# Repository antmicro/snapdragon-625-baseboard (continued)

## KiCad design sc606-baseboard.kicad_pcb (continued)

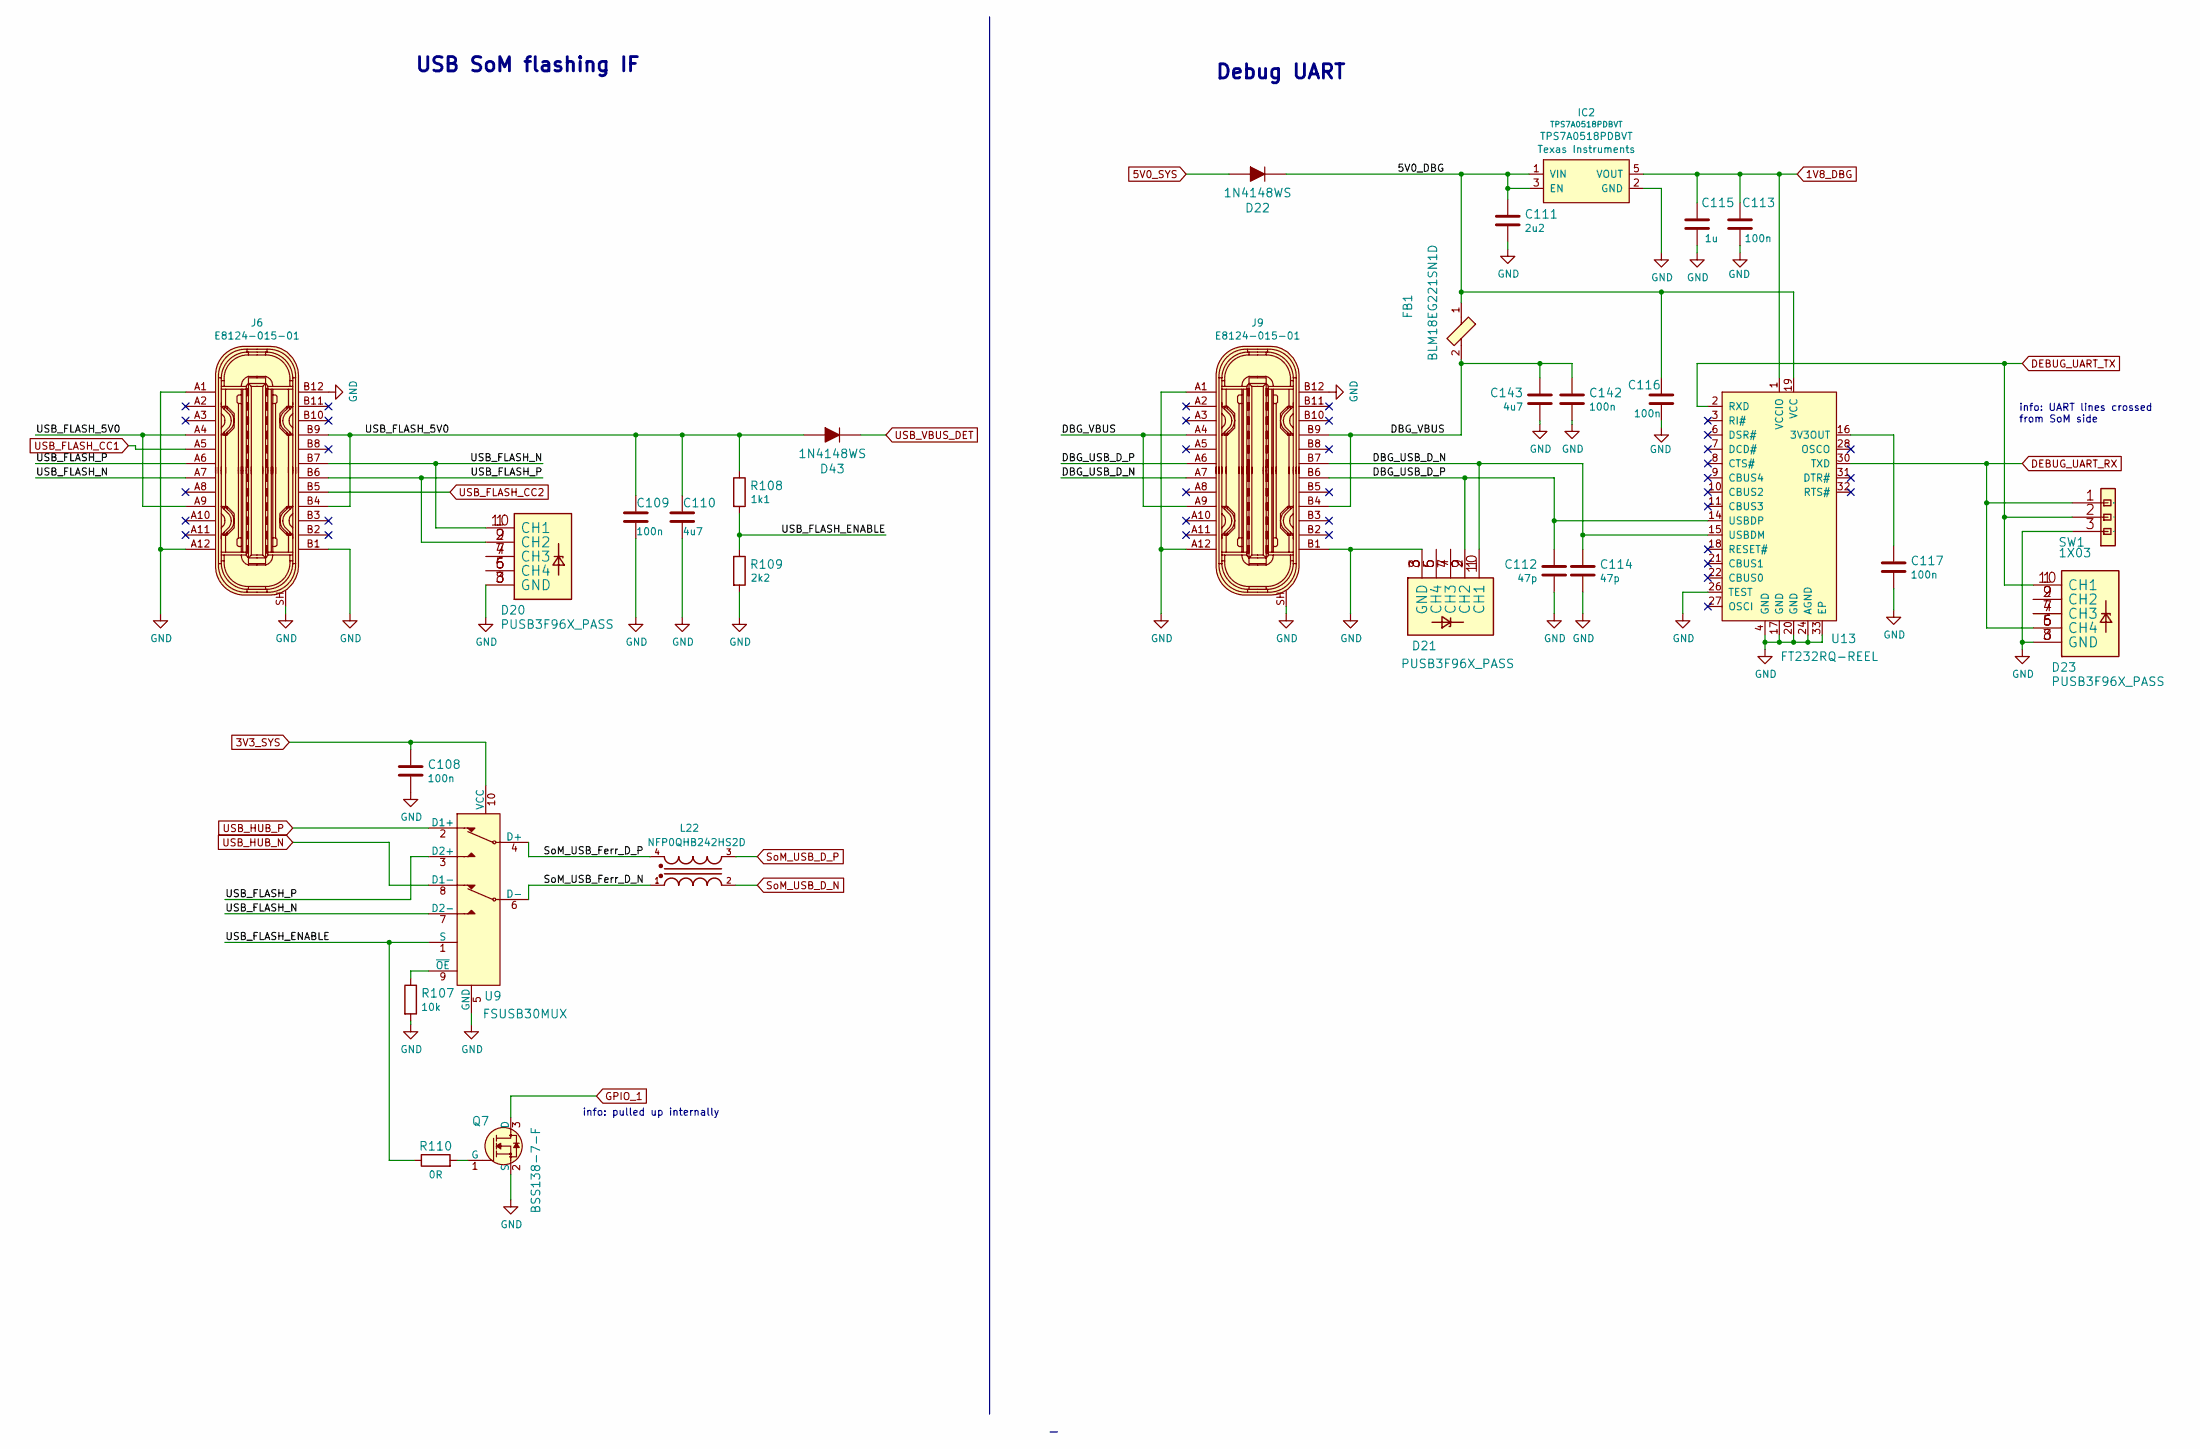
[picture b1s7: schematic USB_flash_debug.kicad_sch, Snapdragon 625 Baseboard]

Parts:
C108, C109, C113, C116, C117, C142: C_100n_0402; 0402-cap; MPN GRM155R61H104KE14D
C110, C143: C_4u7_0402; 0402-cap; MPN GRM155R61A475MEAAD
C111: C_2u2_0402; 0402-cap; MPN C1005X5R1A225K050BC
C112, C114: C_47p_0402; 0402-cap; MPN C0402C470J5GACTU
C115: C_1u_0402; 0402-cap; MPN C1005X6S1A105K050BC
D20, D21, D23: PUSB3F96X_PASS; PUSB3F96X; MPN PUSB3F96X
D22, D43: 1N4148WS; SOD-323F; MPN 1N4148WS
FB1: BLM18EG221SN1D; 0603; MPN BLM18EG221SN1D
IC2: TPS7A0518PDBVT; SOT-23-5; MPN TPS7A0518PDBVT
J6, J9: E8124-015-01; USB-C_Female_E8124-015-01; MPN E8124-015-01
L22: NFP0QHB242HS2D; FIL_NFP0QHB242HS2D; MPN NFP0QHB242HS2D
Q7: BSS138-7-F; SOT-23-3; MPN BSS138-7-F
R107: R_10k_0402; 0402-res; MPN CRCW040210K0FKEDHP
R108: R_1k1_0402; 0402-res; MPN ERJ2RKF1101X
R109: R_2k2_0402; 0402-res; MPN RC0402FR-072K2L
R110: R_0R_0402; 0402-res; MPN ERJ2GE0R00X
SW1: 1X03; MH_1X03_2.54; MPN 61300311121
U9: FSUSB30MUX; MSOP-10_W3mm; MPN FSUSB30MUX
U13: FT232RQ-REEL; QFN-32-1EP_5x5mm; MPN FT232RQ-REEL

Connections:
1V8_DBG: C113.1, C115.1, IC2.5 (VOUT), U13.1 (VCCIO)
3V3_SYS: C108.1, U9.10 (VCC); also elsewhere on the board
5V0_SYS: D22.A; also elsewhere on the board
/USB_flash_debug/5V0_DBG: C111.1, C116.1, D22.K, FB1.1, IC2.1 (VIN), IC2.3 (EN), U13.19 (VCC)
/USB_flash_debug/DBG_USB_D_N: C114.1, D21.1 (CH1), D21.10 (CH1), J9.A7, J9.B7, U13.15 (USBDM)
/USB_flash_debug/DBG_USB_D_P: C112.1, D21.2 (CH2), D21.9 (CH2), J9.A6, J9.B6, U13.14 (USBDP)
/USB_flash_debug/DBG_VBUS: C142.1, C143.1, FB1.2, J9.A4, J9.A9, J9.B4, J9.B9
/USB_flash_debug/SoM_USB_Ferr_D_N: L22.1, U9.6 (D-)
/USB_flash_debug/SoM_USB_Ferr_D_P: L22.4, U9.4 (D+)
/USB_flash_debug/USB_FLASH_5V0: C109.1, C110.1, D43.A, J6.A4, J6.A9, J6.B4, J6.B9, R108.1
/USB_flash_debug/USB_FLASH_ENABLE: R108.2, R109.1, R110.1, U9.1 (S)
/USB_flash_debug/USB_FLASH_N: D20.1 (CH1), D20.10 (CH1), J6.A7, J6.B7, U9.7 (D2-)
/USB_flash_debug/USB_FLASH_P: D20.2 (CH2), D20.9 (CH2), J6.A6, J6.B6, U9.3 (D2+)
DEBUG_UART_RX: D23.5 (CH4), D23.6 (CH4), SW1.1, U13.30 (TXD); also elsewhere on the board
DEBUG_UART_TX: D23.1 (CH1), D23.10 (CH1), SW1.2, U13.2 (RXD); also elsewhere on the board
GND: C108.2, C109.2, C110.2, C111.2, C112.2, C113.2, C114.2, C115.2, C116.2, C117.1, C142.2, C143.2, D20.3 (GND), D20.8 (GND), D21.3 (GND), D21.8 (GND), D23.3 (GND), D23.8 (GND), IC2.2 (GND), J6.A1, J6.A12, J6.B1, J6.B12, J6.SH, J9.A1, J9.A12, J9.B1, J9.B12, J9.SH, Q7.2 (S), R107.2, R109.2, SW1.3, U9.5 (GND), U13.4 (GND), U13.17 (GND), U13.20 (GND), U13.24 (AGND), U13.26 (TEST), U13.33 (EP); also elsewhere on the board
GPIO_1: Q7.3 (D); also elsewhere on the board
unnamed: C117.2, U13.16 (3V3OUT)
unnamed: D20.4 (CH3), D20.7 (CH3)
unnamed: D20.5 (CH4), D20.6 (CH4)
unnamed: D21.4 (CH3), D21.7 (CH3)
unnamed: D21.5 (CH4), D21.6 (CH4)
unnamed: D23.2 (CH2), D23.9 (CH2)
unnamed: D23.4 (CH3), D23.7 (CH3)
unnamed: Q7.1 (G), R110.2
unnamed: R107.1, U9.9 (~OE)
SoM_USB_D_N: L22.2; also elsewhere on the board
SoM_USB_D_P: L22.3; also elsewhere on the board
USB_FLASH_CC1: J6.A5; also elsewhere on the board
USB_FLASH_CC2: J6.B5; also elsewhere on the board
USB_HUB_N: U9.8 (D1-); also elsewhere on the board
USB_HUB_P: U9.2 (D1+); also elsewhere on the board
USB_VBUS_DET: D43.K; also elsewhere on the board

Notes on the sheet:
info: UART lines crossed from SoM side
info: pulled up internally
Debug UART
USB SoM flashing IF

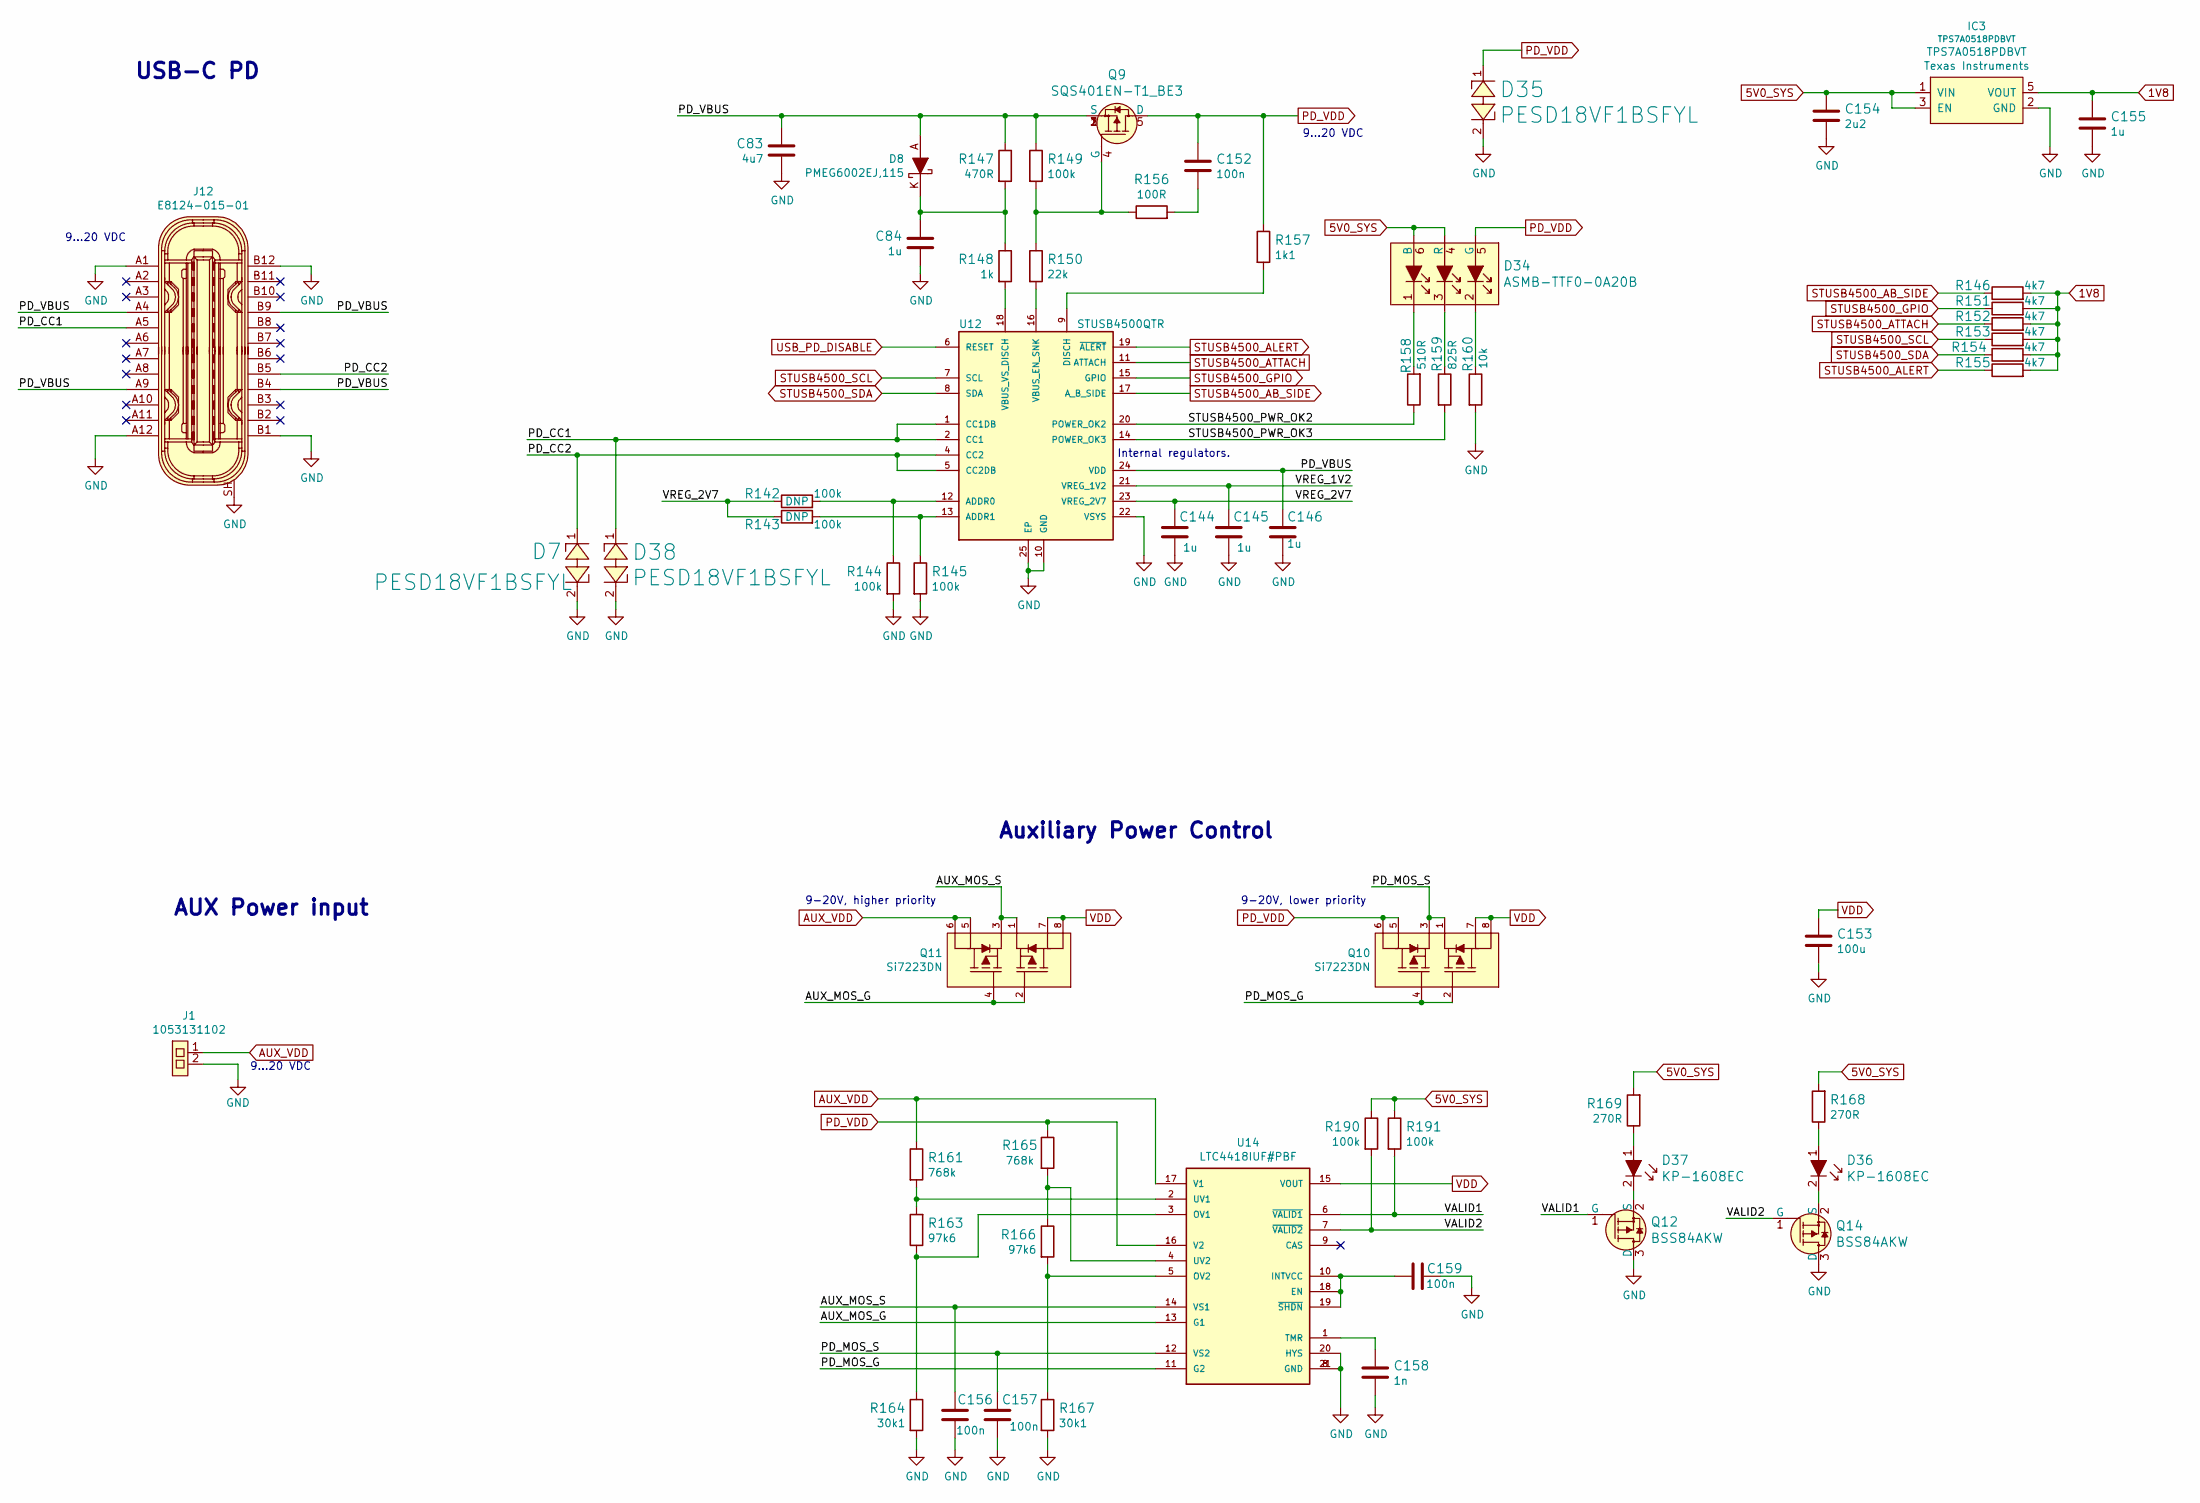
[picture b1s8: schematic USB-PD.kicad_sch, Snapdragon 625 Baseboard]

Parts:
C83: C_4u7_0603; 0603-cap; MPN C1608X5R1V475M080AC
C84: C_1u_0603; 0603-cap; MPN 0603YD105KAT2A
C144, C145, C146, C155: C_1u_0402; 0402-cap; MPN C1005X6S1A105K050BC
C152, C156, C157, C159: C_100n_0402; 0402-cap; MPN GRM155R61H104KE14D
C153: C_100u_0805; 0805-cap; MPN GRM21BR60J107ME15L
C154: C_2u2_0402; 0402-cap; MPN C1005X5R1A225K050BC
C158: C_1n_0402; 0402-res; MPN CC0402KRX7R9BB102
D7, D35, D38: PESD18VF1BSFYL; RESC0603X26N; MPN PESD18VF1BSFYL
D8: PMEG6002EJ,115; SOD-323F; MPN PMEG6002EJ,115
D34: ASMB-TTF0-0A20B; PLCC6_3.5x3.7mm; MPN ASMB-TTF0-0A20B
D36, D37: KP-1608EC; LED_0603; MPN KP-1608EC
IC3: TPS7A0518PDBVT; SOT-23-5; MPN TPS7A0518PDBVT
J1: 1053131102; MPN 1053131102
J12: E8124-015-01; USB-C_Female_E8124-015-01; MPN E8124-015-01
Q9: SQS401EN-T1_BE3; Vishay_PowerPAK_1212-8_Single; MPN SQS401EN-T1_BE3
Q10, Q11: Si7223DN; PowerPak-1212; MPN SI7223DN-T1-GE3
Q12, Q14: BSS84AKW; SOT-323; MPN BSS84AKW,115
R142, R143, R144, R145, R149, R190, R191: R_100k_0402; 0402-res; MPN CRCW0402100KFKEDHP
R146, R151, R152, R153, R154, R155: R_4k7_0402; 0402-res; MPN MCS04020C4701FE000
R147: R_470R_0402; 0402-res; MPN CRCW0402470RFKED
R148: R_1k_0402; 0402-res; MPN CR0402-FX-1001GLF
R150: R_22k_0402; 0402-res; MPN ERJ-2RKF2202X
R156: R_100R_0402; 0402-res; MPN CR0402-FX-1000GLF
R157: R_1k1_0402; 0402-res; MPN ERJ2RKF1101X
R158: R_510R_0402; 0402-res; MPN RC0402JR-07510RL
R159: R_825R_0402; 0402-res; MPN ERJ2RKF8250X
R160: R_10k_0402; 0402-res; MPN CRCW040210K0FKEDHP
R161, R165: R_768k_0402; 0402-res; MPN CRCW0402768KFKED
R163, R166: R_97k6_0402; 0402-res; MPN MCMR04X9762FTL
R164, R167: R_30k1_0603; 0603-res; MPN CRCW060330K1FKEA
R168, R169: R_270R_0603; 0603-res; MPN ERJ3EKF2700V
U12: STUSB4500QTR; QFN50P400X400X90-25N; MPN STUSB4500QTR
U14: LTC4418IUF#PBF; QFN-20_1EP_4x4_P0.5mm; MPN LTC4418IUF#PBF

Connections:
1V8: C155.1, IC3.5 (VOUT), R146.2, R151.2, R152.2, R153.2, R154.2, R155.2
5V0_SYS: C154.1, D34.4 (R), D34.6 (B), IC3.1 (VIN), IC3.3 (EN), R168.2, R169.2, R190.1, R191.1; also elsewhere on the board
/USB-PD/AUX_MOS_G: Q11.2, Q11.4, U14.13 (G1)
/USB-PD/AUX_MOS_S: C156.2, Q11.1, Q11.3, U14.14 (VS1)
/USB-PD/PD_CC1: D38.1, J12.A5, U12.1 (CC1DB), U12.2 (CC1)
/USB-PD/PD_CC2: D7.1, J12.B5, U12.4 (CC2), U12.5 (CC2DB)
/USB-PD/PD_MOS_G: Q10.2, Q10.4, U14.11 (G2)
/USB-PD/PD_MOS_S: C157.2, Q10.1, Q10.3, U14.12 (VS2)
/USB-PD/PD_VBUS: C83.1, C146.1, D8.A, J12.A4, J12.A9, J12.B4, J12.B9, Q9.1 (S), Q9.2 (S), Q9.3 (S), R147.1, R149.1, U12.24 (VDD)
/USB-PD/STUSB4500_PWR_OK2: R158.1, U12.20 (POWER_OK2)
/USB-PD/STUSB4500_PWR_OK3: R159.2, U12.14 (POWER_OK3)
/USB-PD/VALID1: Q12.1 (G), R191.2, U14.6 (~VALID1)
/USB-PD/VALID2: Q14.1 (G), R190.2, U14.7 (~VALID2)
/USB-PD/VREG_1V2: C145.2, U12.21 (VREG_1V2)
/USB-PD/VREG_2V7: C144.1, R142.1, R143.1, U12.23 (VREG_2V7)
AUX_VDD: J1.1, Q11.5, Q11.6, R161.1, U14.17 (V1)
GND: C83.2, C84.2, C144.2, C145.1, C146.2, C153.2, C154.2, C155.2, C156.1, C157.1, C158.2, C159.1, D7.2, D35.2, D38.2, IC3.2 (GND), J1.2, J12.A1, J12.A12, J12.B1, J12.B12, J12.SH, Q12.3 (D), Q14.3 (D), R144.2, R145.2, R160.2, R164.2, R167.2, U12.10 (GND), U12.22 (VSYS), U12.25 (EP), U14.8 (GND), U14.20 (HYS), U14.21 (GND); also elsewhere on the board
unnamed: C84.1, D8.K, R147.2, R148.1
unnamed: C152.2, R156.2
unnamed: C158.1, U14.1 (TMR)
unnamed: C159.2, U14.10 (INTVCC), U14.18 (EN), U14.19 (~SHDN)
unnamed: D34.1, R158.2
unnamed: D34.2, R160.1
unnamed: D34.3, R159.1
unnamed: D36.1, R168.1
unnamed: D36.2, Q14.2 (S)
unnamed: D37.1, R169.1
unnamed: D37.2, Q12.2 (S)
unnamed: Q9.4 (G), R149.2, R150.1, R156.1
unnamed: R142.2, R144.1, U12.12 (ADDR0)
unnamed: R143.2, R145.1, U12.13 (ADDR1)
unnamed: R148.2, U12.18 (VBUS_VS_DISCH)
unnamed: R150.2, U12.16 (VBUS_EN_SNK)
unnamed: R157.2, U12.9 (DISCH)
unnamed: R161.2, R163.2, U14.2 (UV1)
unnamed: R163.1, R164.1, U14.3 (OV1)
unnamed: R165.2, R166.1, U14.4 (UV2)
unnamed: R166.2, R167.1, U14.5 (OV2)
PD_VDD: C152.1, D34.5 (G), D35.1, Q9.5 (D), Q10.5, Q10.6, R157.1, R165.1, U14.16 (V2)
STUSB4500_AB_SIDE: R146.1, U12.17 (A_B_SIDE)
STUSB4500_ALERT: R155.1, U12.19 (~ALERT)
STUSB4500_ATTACH: R152.1, U12.11 (ATTACH)
STUSB4500_GPIO: R151.1, U12.15 (GPIO)
STUSB4500_SCL: R153.1, U12.7 (SCL); also elsewhere on the board
STUSB4500_SDA: R154.1, U12.8 (SDA); also elsewhere on the board
USB_PD_DISABLE: U12.6 (RESET)
VDD: C153.1, Q10.7, Q10.8, Q11.7, Q11.8, U14.15 (VOUT); also elsewhere on the board

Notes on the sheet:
9...20 VDC
9-20V, lower priority
USB-C PD
Auxiliary Power Control
Internal regulators.
AUX Power input
9-20V, higher priority

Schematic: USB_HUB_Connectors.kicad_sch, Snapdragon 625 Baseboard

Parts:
C94, C102, C103, C118, C120, C121, C122, C123, C124, C125, C126, C127, C128, C129, C131, C134, C140, C141, C147, C148, C149, C150, C151: C_100n_0402; 0402-cap; MPN GRM155R61H104KE14D
C119: C_4u7_0402; 0402-cap; MPN GRM155R61A475MEAAD
C130, C136: C_1u_0402; 0402-cap; MPN C1005X6S1A105K050BC
C132, C137, C160: C_10u_0402; 0402-cap; MPN CC0402MRX5R5BB106
C133, C135: C_15p_0402; 0402-cap; MPN MC0402N150J500CT
C139, C161, C170: C_100u_0805; 0805-cap; MPN GRM21BR60J107ME15L
D24: KP-1608EC; LED_0603; MPN KP-1608EC
D25, D26, D27, D28, D31, D32: PUSB3F96X_PASS; PUSB3F96X; MPN PUSB3F96X
FB2: BLM18EG221SN1D; 0603; MPN BLM18EG221SN1D
IC4: AP22652W6-7; SOT-23-6; MPN AP22652W6-7
J10, J11: E8124-015-01; USB-C_Female_E8124-015-01; MPN E8124-015-01
R112, R122, R124, R130, R133, R134, R135, R136, R137, R174: R_0R_0402; 0402-res; MPN ERJ2GE0R00X
R113: R_12k_1%_0603; 0603-res; MPN MCWR06X1202FTL
R114, R115, R116, R117, R118: R_20k_0402; 0402-res; MPN CRCW040220K0FKED
R119, R120: R_200k_0402; 0402-res; MPN RC0402FR-07200KL
R121: R_1M0_0402; 0402-res; MPN CRG0402F1M0
R123, R125, R131, R132, R138, R139, R140, R141: R_56k_0402; 0402-res; MPN CRCW040256K0FKED
R171: R_10k_0402; 0402-res; MPN CRCW040210K0FKEDHP
R172: R_470R_0402; 0402-res; MPN CRCW0402470RFKED
R173: R_12k4_0402; 0402-res; MPN ERJ2RKF1242X
TP13, TP14, TP15, TP16, TP17, TP18, TP19, TP20, TP23, TP24: TP_SMD_1_5MM; TP-R-1.5
U15: USB57442G; QFN40P700X700X100-57N; MPN USB5744
Y2: ABM8G-25.000MHZ-B4Y-T; KX-7; MPN ABM8G-25.000MHZ-B4Y-T

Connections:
1V2_SYS: C120.2, C121.2, C123.2, C125.2, C127.2, C129.2, C131.2, C134.2, C136.1, C137.1, U15.5 (VDD12), U15.12 (VDD12), U15.15 (VDD12), U15.21 (VDD12), U15.28 (VDD12), U15.33 (VDD12), U15.43 (VDD12), U15.49 (VDD12); also elsewhere on the board
3V3_SYS: C118.1, C119.1, C122.1, C124.1, C126.1, C128.1, C130.2, C132.2, R118.1, U15.16 (VDD33), U15.31 (VDD33), U15.37 (VBUS_DET/GPIO16), U15.44 (VDD33), U15.55 (VDD33); also elsewhere on the board
5V0_SYS: C160.1, IC4.1 (IN), R171.1, R172.1, R174.1; also elsewhere on the board
/USB_HUB_Connectors/5V0_USB: C103.1, C139.1, C151.2, C170.2, FB2.2, J10.A4, J10.A9, J10.B4, J10.B9, J11.A4, J11.A9, J11.B4, J11.B9, R123.1, R131.1, R138.1, R140.1, R174.2, TP20.1
/USB_HUB_Connectors/HUB_XTALI: C133.2, R121.1, U15.54 (XTALI/CLK_IN), Y2.1
/USB_HUB_Connectors/HUB_XTALO: C135.2, R121.2, U15.53 (XTALO), Y2.3
/USB_HUB_Connectors/SPI_CE: R119.2, TP14.1, U15.41 (SPI_CE_N/CFG_NON_REM/GPIO7)
/USB_HUB_Connectors/SPI_CLK: TP16.1, U15.38 (SPI_CLK/SMCLK/GPIO4)
/USB_HUB_Connectors/SPI_DI: R120.2, TP15.1, U15.40 (SPI_DI/CFG_BC_EN/GPIO9)
/USB_HUB_Connectors/SPI_DO: TP17.1, U15.39 (SPI_DO/SMDAT/GPIO5)
/USB_HUB_Connectors/USB_C1_CC1: J10.A5, R123.2, R125.1
/USB_HUB_Connectors/USB_C1_CC2: J10.B5, R131.2, R132.1
/USB_HUB_Connectors/USB_C1_D1_N: D27.4 (CH3), D27.7 (CH3), J10.A7, U15.9 (USB2DN_DM2/PRT_DIS_M2)
/USB_HUB_Connectors/USB_C1_D1_P: D27.5 (CH4), D27.6 (CH4), J10.A6, U15.8 (USB2DN_DP2/PRT_DIS_P2)
/USB_HUB_Connectors/USB_C1_D2_N: D28.4 (CH3), D28.7 (CH3), J10.B7, U15.2 (USB2DN_DM1/PRT_DIS_M1)
/USB_HUB_Connectors/USB_C1_D2_P: D28.5 (CH4), D28.6 (CH4), J10.B6, U15.1 (USB2DN_DP1/PRT_DIS_P1)
/USB_HUB_Connectors/USB_C1_SS_C_RX1_N: D28.1 (CH1), D28.10 (CH1), J10.B10, R133.2
/USB_HUB_Connectors/USB_C1_SS_C_RX1_P: D28.2 (CH2), D28.9 (CH2), J10.B11, R130.2
/USB_HUB_Connectors/USB_C1_SS_C_RX2_N: D27.2 (CH2), D27.9 (CH2), J10.A10, R124.2
/USB_HUB_Connectors/USB_C1_SS_C_RX2_P: D27.1 (CH1), D27.10 (CH1), J10.A11, R122.2
/USB_HUB_Connectors/USB_C1_SS_C_TX1_N: C102.1, D25.4 (CH3), D25.7 (CH3), J10.A3
/USB_HUB_Connectors/USB_C1_SS_C_TX1_P: C94.1, D25.5 (CH4), D25.6 (CH4), J10.A2
/USB_HUB_Connectors/USB_C1_SS_C_TX2_N: C140.1, D25.2 (CH2), D25.9 (CH2), J10.B3
/USB_HUB_Connectors/USB_C1_SS_C_TX2_P: C141.1, D25.1 (CH1), D25.10 (CH1), J10.B2
/USB_HUB_Connectors/USB_C1_SS_RX1_N: R133.1, U15.14 (USB3DN_RXDM2)
/USB_HUB_Connectors/USB_C1_SS_RX1_P: R130.1, U15.13 (USB3DN_RXDP2)
/USB_HUB_Connectors/USB_C1_SS_RX2_N: R124.1, U15.7 (USB3DN_RXDM1)
/USB_HUB_Connectors/USB_C1_SS_RX2_P: R122.1, U15.6 (USB3DN_RXDP1)
/USB_HUB_Connectors/USB_C1_SS_TX1_N: C102.2, U15.11 (USB3DN_TXDM2)
/USB_HUB_Connectors/USB_C1_SS_TX1_P: C94.2, U15.10 (USB3DN_TXDP2)
/USB_HUB_Connectors/USB_C1_SS_TX2_N: C140.2, U15.4 (USB3DN_TXDM1)
/USB_HUB_Connectors/USB_C1_SS_TX2_P: C141.2, U15.3 (USB3DN_TXDP1)
/USB_HUB_Connectors/USB_C2_CC1: J11.A5, R138.2, R139.1
/USB_HUB_Connectors/USB_C2_CC2: J11.B5, R140.2, R141.1
/USB_HUB_Connectors/USB_C2_D1_N: D31.1 (CH1), D31.10 (CH1), J11.A7, U15.18 (USB2DN_DM3/PRT_DIS_M3)
/USB_HUB_Connectors/USB_C2_D1_P: D31.2 (CH2), D31.9 (CH2), J11.A6, U15.17 (USB2DN_DP3/PRT_DIS_P3)
/USB_HUB_Connectors/USB_C2_D2_N: D26.2 (CH2), D26.9 (CH2), J11.B7, U15.25 (USB2DN_DM4/PRT_DIS_M4)
/USB_HUB_Connectors/USB_C2_D2_P: D26.1 (CH1), D26.10 (CH1), J11.B6, U15.24 (USB2DN_DP4/PRT_DIS_P4)
/USB_HUB_Connectors/USB_C2_SS_C_RX1_N: D31.4 (CH3), D31.7 (CH3), J11.B10, R137.2
/USB_HUB_Connectors/USB_C2_SS_C_RX1_P: D31.5 (CH4), D31.6 (CH4), J11.B11, R136.2
/USB_HUB_Connectors/USB_C2_SS_C_RX2_N: D32.2 (CH2), D32.9 (CH2), J11.A10, R135.2
/USB_HUB_Connectors/USB_C2_SS_C_RX2_P: D32.1 (CH1), D32.10 (CH1), J11.A11, R134.2
/USB_HUB_Connectors/USB_C2_SS_C_TX1_N: C149.1, D26.4 (CH3), D26.7 (CH3), J11.A3
/USB_HUB_Connectors/USB_C2_SS_C_TX1_P: C147.1, D26.5 (CH4), D26.6 (CH4), J11.A2
/USB_HUB_Connectors/USB_C2_SS_C_TX2_N: C150.1, D32.4 (CH3), D32.7 (CH3), J11.B3
/USB_HUB_Connectors/USB_C2_SS_C_TX2_P: C148.1, D32.5 (CH4), D32.6 (CH4), J11.B2
/USB_HUB_Connectors/USB_C2_SS_RX1_N: R137.1, U15.23 (USB3DN_RXDM3)
/USB_HUB_Connectors/USB_C2_SS_RX1_P: R136.1, U15.22 (USB3DN_RXDP3)
/USB_HUB_Connectors/USB_C2_SS_RX2_N: R135.1, U15.30 (USB3DN_RXDM4)
/USB_HUB_Connectors/USB_C2_SS_RX2_P: R134.1, U15.29 (USB3DN_RXDP4)
/USB_HUB_Connectors/USB_C2_SS_TX1_N: C149.2, U15.20 (USB3DN_TXDM3)
/USB_HUB_Connectors/USB_C2_SS_TX1_P: C147.2, U15.19 (USB3DN_TXDP3)
/USB_HUB_Connectors/USB_C2_SS_TX2_N: C150.2, U15.27 (USB3DN_TXDM4)
/USB_HUB_Connectors/USB_C2_SS_TX2_P: C148.2, U15.26 (USB3DN_TXDP4)
GND: C103.2, C118.2, C119.2, C120.1, C121.1, C122.2, C123.1, C124.2, C125.1, C126.2, C127.1, C128.2, C129.1, C130.1, C131.1, C132.1, C133.1, C134.1, C135.1, C136.2, C137.2, C139.2, C151.1, C160.2, C161.2, C170.1, D25.3 (GND), D25.8 (GND), D26.3 (GND), D26.8 (GND), D27.3 (GND), D27.8 (GND), D28.3 (GND), D28.8 (GND), D31.3 (GND), D31.8 (GND), D32.3 (GND), D32.8 (GND), IC4.2 (GND), J10.A1, J10.A12, J10.B1, J10.B12, J10.SH, J11.A1, J11.A12, J11.B1, J11.B12, J11.SH, R112.1, R113.1, R114.1, R115.1, R116.1, R117.1, R119.1, R120.1, R125.2, R132.2, R139.2, R141.2, R173.2, U15.57 (VSS), Y2.2, Y2.4; also elsewhere on the board
unnamed: C161.1, FB2.1, IC4.6 (OUT)
unnamed: D24.1, R172.2
unnamed: D24.2, IC4.4 (~FAULT)
unnamed: IC4.3 (EN), R171.2
unnamed: IC4.5 (ILIM), R173.1
unnamed: J10.A8, TP18.1
unnamed: J10.B8, TP19.1
unnamed: J11.A8, TP23.1
unnamed: J11.B8, TP24.1
unnamed: R112.2, TP13.1, U15.52 (ATEST)
unnamed: R113.2, U15.56 (RBIAS)
unnamed: R114.2, U15.36 (PRT_CTL1)
unnamed: R115.2, U15.35 (PRT_CTL2)
unnamed: R116.2, U15.34 (PRT_CTL3)
unnamed: R117.2, U15.32 (PRT_CTL4/GANG_PWR)
unnamed: R118.2, U15.42 (RESET_N)
SoM_USB3_RX_N: U15.48 (USB3UP_TXDM); also elsewhere on the board
SoM_USB3_RX_P: U15.47 (USB3UP_TXDP); also elsewhere on the board
SoM_USB3_TX_N: U15.51 (USB3UP_RXDM); also elsewhere on the board
SoM_USB3_TX_P: U15.50 (USB3UP_RXDP); also elsewhere on the board
USB_HUB_N: U15.46 (USB2UP_DM); also elsewhere on the board
USB_HUB_P: U15.45 (USB2UP_DP); also elsewhere on the board

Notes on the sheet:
ESD Protection
USB-C Connectors
USB HUB
USB-C connector 2
USB-C connector 1
USB Load Switch

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
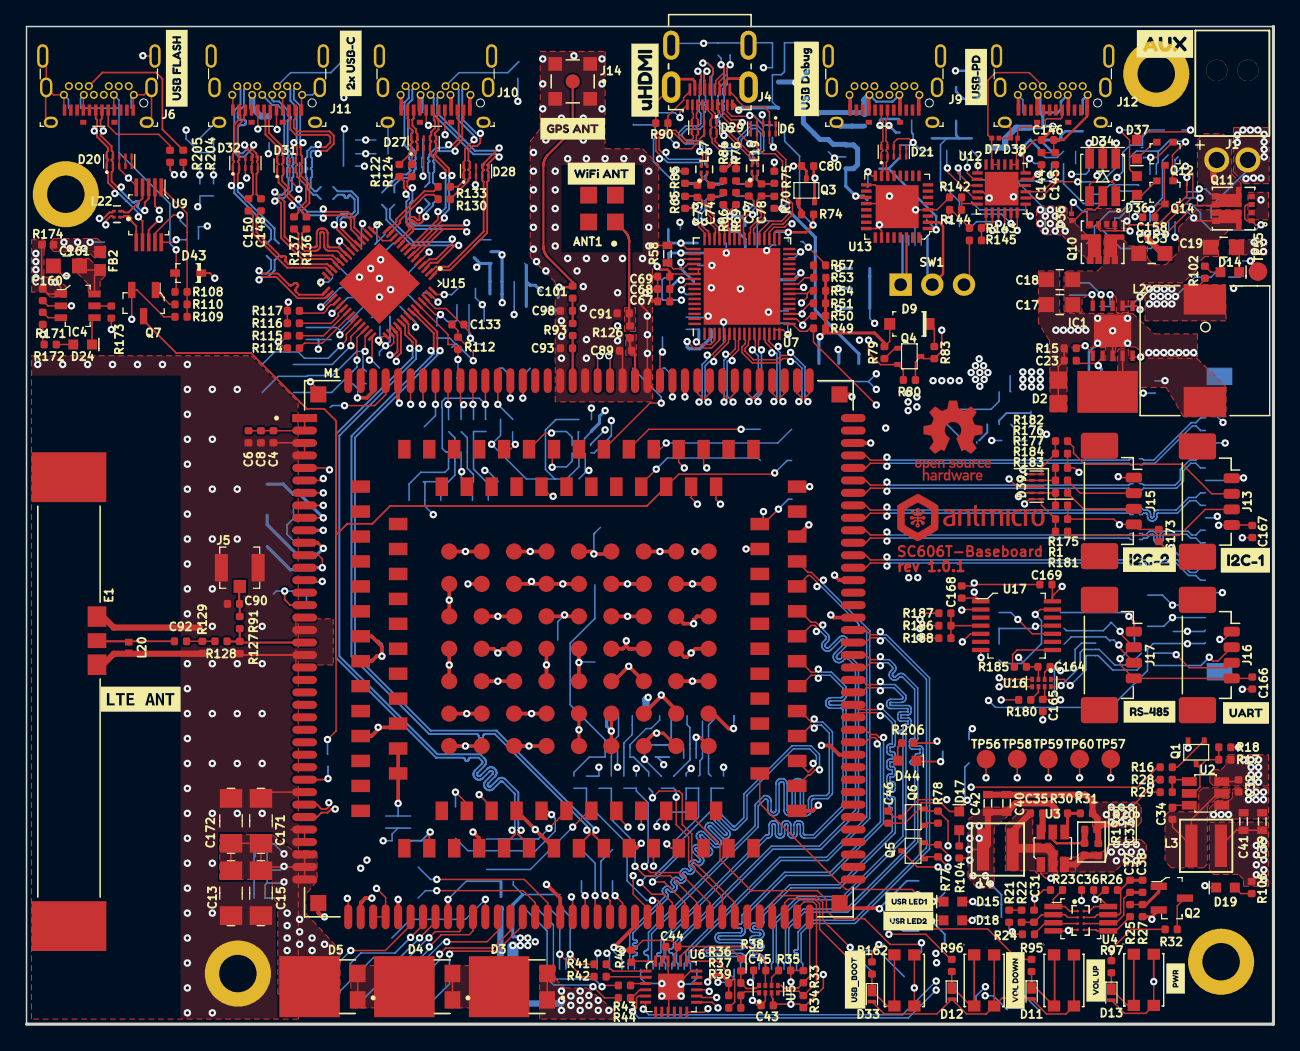
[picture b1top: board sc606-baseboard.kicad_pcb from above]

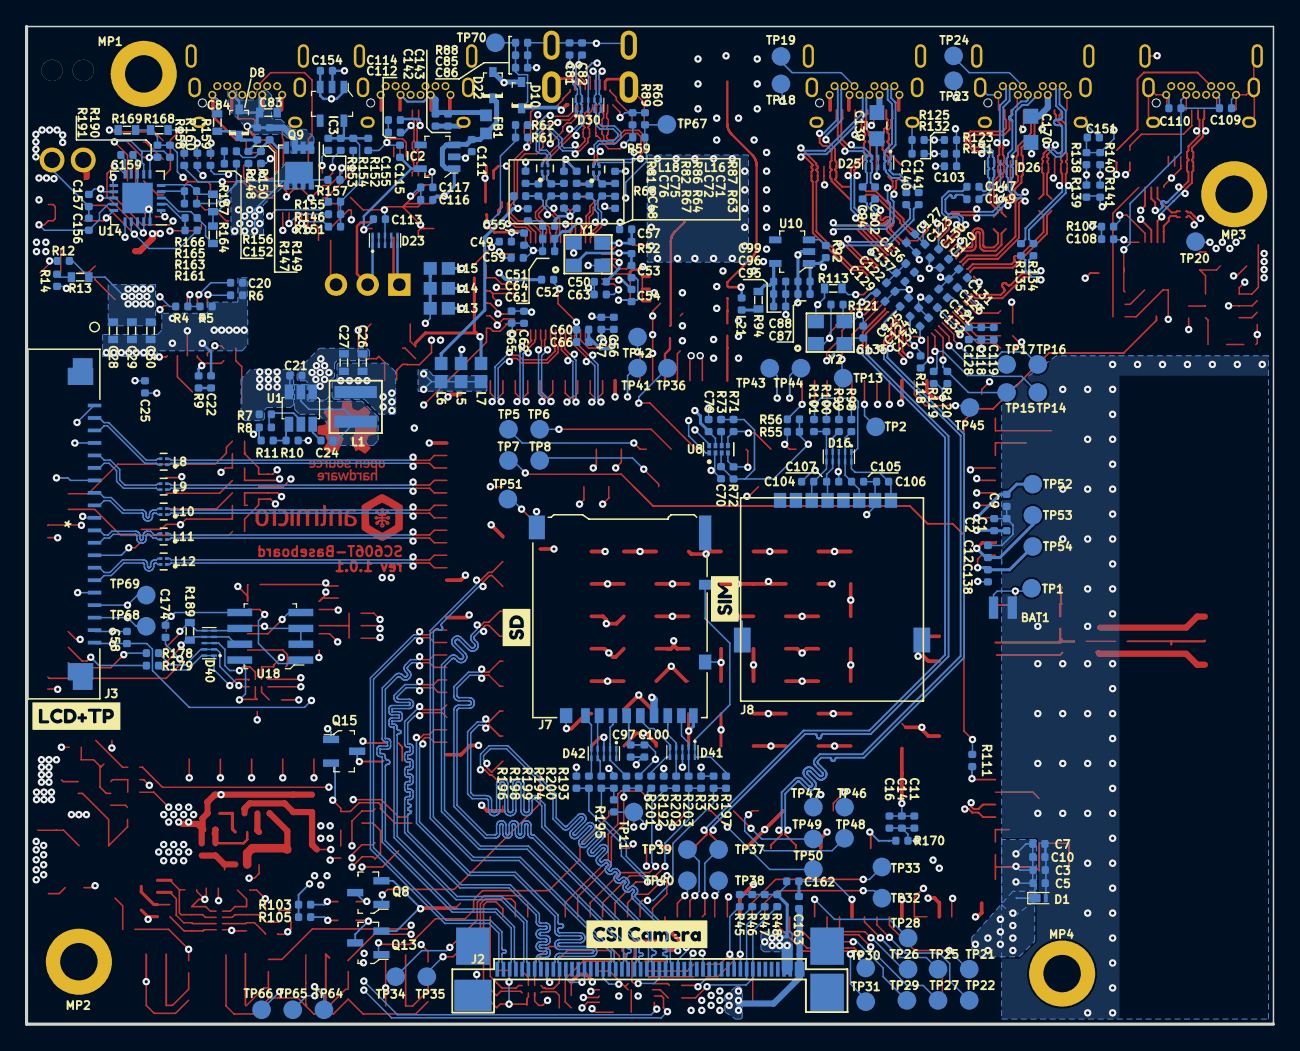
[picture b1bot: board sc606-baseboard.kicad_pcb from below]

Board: 6 copper layers, 100.0 x 80.0 mm, 604 parts (328 on the bottom side), 437 nets.

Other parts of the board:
D3, D4, D5: V8PM45-M3_H; TO-277A
kibuzzard-620F6B6A, kibuzzard-620F6BA8, kibuzzard-620F6C9E, kibuzzard-620F6CD0, kibuzzard-620F6D4D, kibuzzard-620F6D7B, kibuzzard-620F6D8B, kibuzzard-620F6D37, kibuzzard-620F6DAB, kibuzzard-620F6E02, kibuzzard-620F6E12, kibuzzard-620F6E26, kibuzzard-620F6E33, kibuzzard-620F6EEA, kibuzzard-620F7ADA, kibuzzard-620F7AEB, kibuzzard-620F7AFE, kibuzzard-620F7B0C, kibuzzard-620F7B15, kibuzzard-620F7B41, kibuzzard-620F79D2, kibuzzard-6200CC83, kibuzzard-6200CCB6: G***; label

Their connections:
5V0_SYS: D3.1, D3.2; also elsewhere on the board
unnamed: D3.3, D4.1, D4.2
unnamed: D4.3, D5.1, D5.2
V_SOM: D5.3; also elsewhere on the board

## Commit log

2022-01-04 Add README
2022-05-10 Added corrections to schemas after review
2022-05-10 LT9611 connected to all needed sources
2022-05-10 Scheme for 5V Main DC/DC converter created
2022-05-10 Added ESD protection to SD card
2022-05-10 Added Auto-On circuit in power_supply.sch
2022-05-10 Block diagram update
2022-05-10 Add Ignore
2022-05-10 update of block diagram, creation of sub-sheets
2022-05-10 Creating schematic of SoM power supply elements
2022-05-10 Rename the block diagram img
2022-05-10 Added keypads and no flag connections to unused pins
2022-05-10 Added scheme for 5V to 3V3 buck
2022-05-10 Add sub-sheets to the design
2022-05-10 Add scheme for SIM card
2022-05-10 Cleanup
2022-05-10 Change DC/DC converters to match project SA800u
2022-05-10 Added annotations. Move to loclib
2022-05-10 Added USB switch along with USB flash connector
2022-05-10 Start of MIPI to HDMI converter schema
2022-05-10 Creating schema for SD card connection
2022-05-10 Added schema of Main and GNSS Antenna
2022-05-10 Creating schemas for camera FFC, connecting related pins to SoM, schema of I2C MUX and voltage transceiver; Adding RESET to power supplies; connecting to SoM 1v8 power output
2022-05-10 Modifications after P. Szczygiel review
2022-05-10 Added TP Interface. Connector must yet be added
2022-05-10 Add LICENSE
2022-05-10 Creating empty kicad project
2022-05-10 Added ESD protection to HDMI
2022-05-10 Finished connection to HDMI interface. Adjustments after Update of LT9611 symbol
2022-05-10 Added 5V to 4V SoM power supply and 5V to 3V3 camera power supply
2022-05-10 Added connectors to LCD displays
2022-05-10 Added connections of both USB A & C connectors
2022-05-10 Main 5V buck converter placed and routed
2022-05-10 Start of creating USB HUB schema
2022-05-10 Added buck converters for 3v3 sys, 3v3 cam, 1v2 lontium. Added auto power-on
2022-05-10 Chip changed for Debug UART. Changed connector from USB-A to USB-C
2022-05-10 Added footprint of 2x USB-A stacked. Added connections to USB HUB.
2022-05-10 Added USB A and C double stack connector
2022-05-10 Adding missing 3D models of components
2022-05-10 Added USC-C connector and first option of debug UART
2022-05-10 FFC and general display camera connectors distributed on board
2022-05-10 Added USB BOOT, placed USR LEDs and buttons, connected Test Points
2022-05-10 Main components placed on board
2022-05-10 Started placing main components on PCB. Change of RT battery model and USB flash connector
2022-05-10 Removed mounting pad for GNSS, changed main antenna model, added wifi ufl connector
2022-05-10 Prepared layout of USB flash and debug components
2022-05-10 Started rearrangement of components. USB connectors changed to 2xUSB-C
2022-05-10 All components placed on board
2022-05-10 Finished component placement
2022-05-10 Finished placement after shortening board by 1cm
2022-05-10 Connected USB-PD and power select chip
2022-05-10 USB Debug changed to micro USB. Started modifications on shortening board by 1cm
2022-05-10 Changed USB flash and debug to USB-C. Prepared place for USB PD. Minor modifications of components position
2022-05-10 Minor updates
2022-05-10 Adjusted position of uHDMI
2022-05-10 Routed USB flash and both USB connectors differential signals with tuning
2022-05-10 Modified position of buttons, SD, SIM and USB connectors. Modified LT9611 footprint
2022-05-10 Routed CAM, LCD, USB Debug differential pairs with tuning
2022-05-10 Connected differential signals from camera modules and LCD display. Without checking track lengths
2022-05-10 Antenna signals routed
2022-05-10 Connected all signals for USB Flash and USB-C connectors
2022-05-10 Finished routing differential pairs. Half of them already tuned
2022-05-10 Changed ESD diode and transistor near USB-PD
2022-05-10 Connected SIM, SD, SoM GNDs
2022-05-10 Connecting LT9611
2022-05-10 Changed barrel jack model, added power path controller
2022-05-10 Cleaned display sch
2022-05-10 Adjusted HDMI-side layout around Lontium chip
2022-05-10 Cleaned/fixed USB flash debug sch
2022-05-10 Tuned and corrected USB lines
2022-05-10 SoM sch cleaned, added testpoints
2022-05-10 Added schema for serial interface connectors
2022-05-10 Cleaned and added testpoints to cameras_module.sch
2022-05-10 Correction in connecting GND pads using Vias, not tracks. Connecting Lontium to power supply
2022-05-10 Tuning CSI an HDMI traacks
2022-05-10 All routes connected
2022-05-10 Corrected DRC errors
2022-05-10 Solved DRC problems with HDMI and CSI
2022-05-10 Cleaned and added testpoints to spoer supply sch
2022-05-10 Corrected power supplies. Change of TP to 1,5mm
2022-05-10 Cleaned serial interfaces
2022-05-10 Corrected serial interface schemas
2022-05-10 Updated image of block diagram
2022-05-10 Added markings for components
2022-05-10 Re-placement of main 5V buck components
2022-05-10 Finished routing serial interface connectors
2022-05-10 Fix STUSB4500 VDD connection, fix DRC error
2022-05-10 Connecting serial interfaces on board
2022-05-10 Production ready, EC-validated
2022-05-10 Schematic cleanup
2022-05-10 Debug connector moved away from chip. Corrected wifi antenna ground plane. Added arcs on GNSS and WiFi tracks
2022-05-10 Schematic cleanup - peripherals and USB-PD
2022-05-10 Removed DRC errors
2022-05-10 Placement of serial interface connectors components
2022-05-10 Schematic cleanup-USB HUB
2022-05-10 Changed name of board from Kibuzzard to Text
2022-05-10 Corrected warnings from EC
2022-05-10 Fixed DRC and other minor errors
2022-05-10 Finished board routing
2022-05-10 Corrected errors from feedback. Added board name, version, Antmicro and OSHW logo, connector labels, button and LED descriptions
2022-05-10 Added alternated footprint for U4. Rev bumped to 1.0.1
2022-05-10 Modified 3D model of coil
2022-05-10 Update SC606T 3D model
2022-05-10 Corrected footprint of Q10 and Q11. Used 'kmake loclib'
2022-05-10 Update USB-C footprint in lib
2022-05-10 Remove obsolete fab files
2022-05-10 Cleanup, start ignoring archives
2022-05-10 Prototyping EC E1408371
2022-05-10 Replaced USB-C port footprint. Fixed traces after changes respectively to DRC.
2022-05-10 README: Add photo
2022-05-10 Update local libraries
2022-05-10 Remove length stats
2022-05-10 Update the sch signage, remove redundant sheets
2022-05-10 Add PDF schematic
2022-05-12 Connected STUSB4500 I2C to SoM. Exchanged ESD protection for SD card
2022-05-25 Removed Q8, R111. SoM_USB_FLASH_ID changed from SoM's USB_ID to GPIO_1. Connected flash CC to SoM through 0R. Connected USB_VBUS to USB flash 5V via diode. SoM USB_ID connected to GPIO_1 through 0R
2022-05-25 Added N-FETs to control USR_LEDs. Reconnected them to 3V3 power supply. Added LED indicating SoM turns on
2022-05-26 Notes added by 'git notes add'
2022-05-27 resize image
2022-06-03 Convert README to .md, added badge
2022-07-15 Converted to KiCad 6. Corrected BUSes. Changed voltage supply for SOM. Checked DRC
2022-07-15 Cleared old files. Added 0R after DCDC converters
2023-08-02 [#47567] Generate docfiles
2023-11-08 Introduce component standardization
2023-11-08 Add OHP assets
2023-11-08 [#47567] Improve intra skew of USB lanes
2023-11-08 [#47567] Correct 5V0_SYS copper fill
    Reroute 3V3_SYS pm In2 layer
2023-11-08 Tweak 5V0_SYS connection to the IC4
2023-11-08 [#47567] Add copper patch to make 5V0_SYS wider
2023-11-08 Added stackup info to pcb file
2023-11-08 [#47567] Correct copper fills
2023-11-08 Correct 3V3_SYS connection to the USB hub
2023-11-08 Update OHP assets 51078
2024-07-03 [#61796] Run globlib
2024-07-08 [#61796] Update schematics
2024-07-08 [#61796] Clean ERC
2024-07-08 [#61796] Update PCB
2024-07-09 [#61796] Clean DRC
2024-07-10 [#61796] Update designators
2024-07-10 [#61796] Update layer names
2024-07-10 [#61796] Update README.md
2024-07-10 [#61796] Remove lib
2024-07-12 [#61796] Regenerate OHP assets
2024-07-12 [#61796] Remove link to loclib
